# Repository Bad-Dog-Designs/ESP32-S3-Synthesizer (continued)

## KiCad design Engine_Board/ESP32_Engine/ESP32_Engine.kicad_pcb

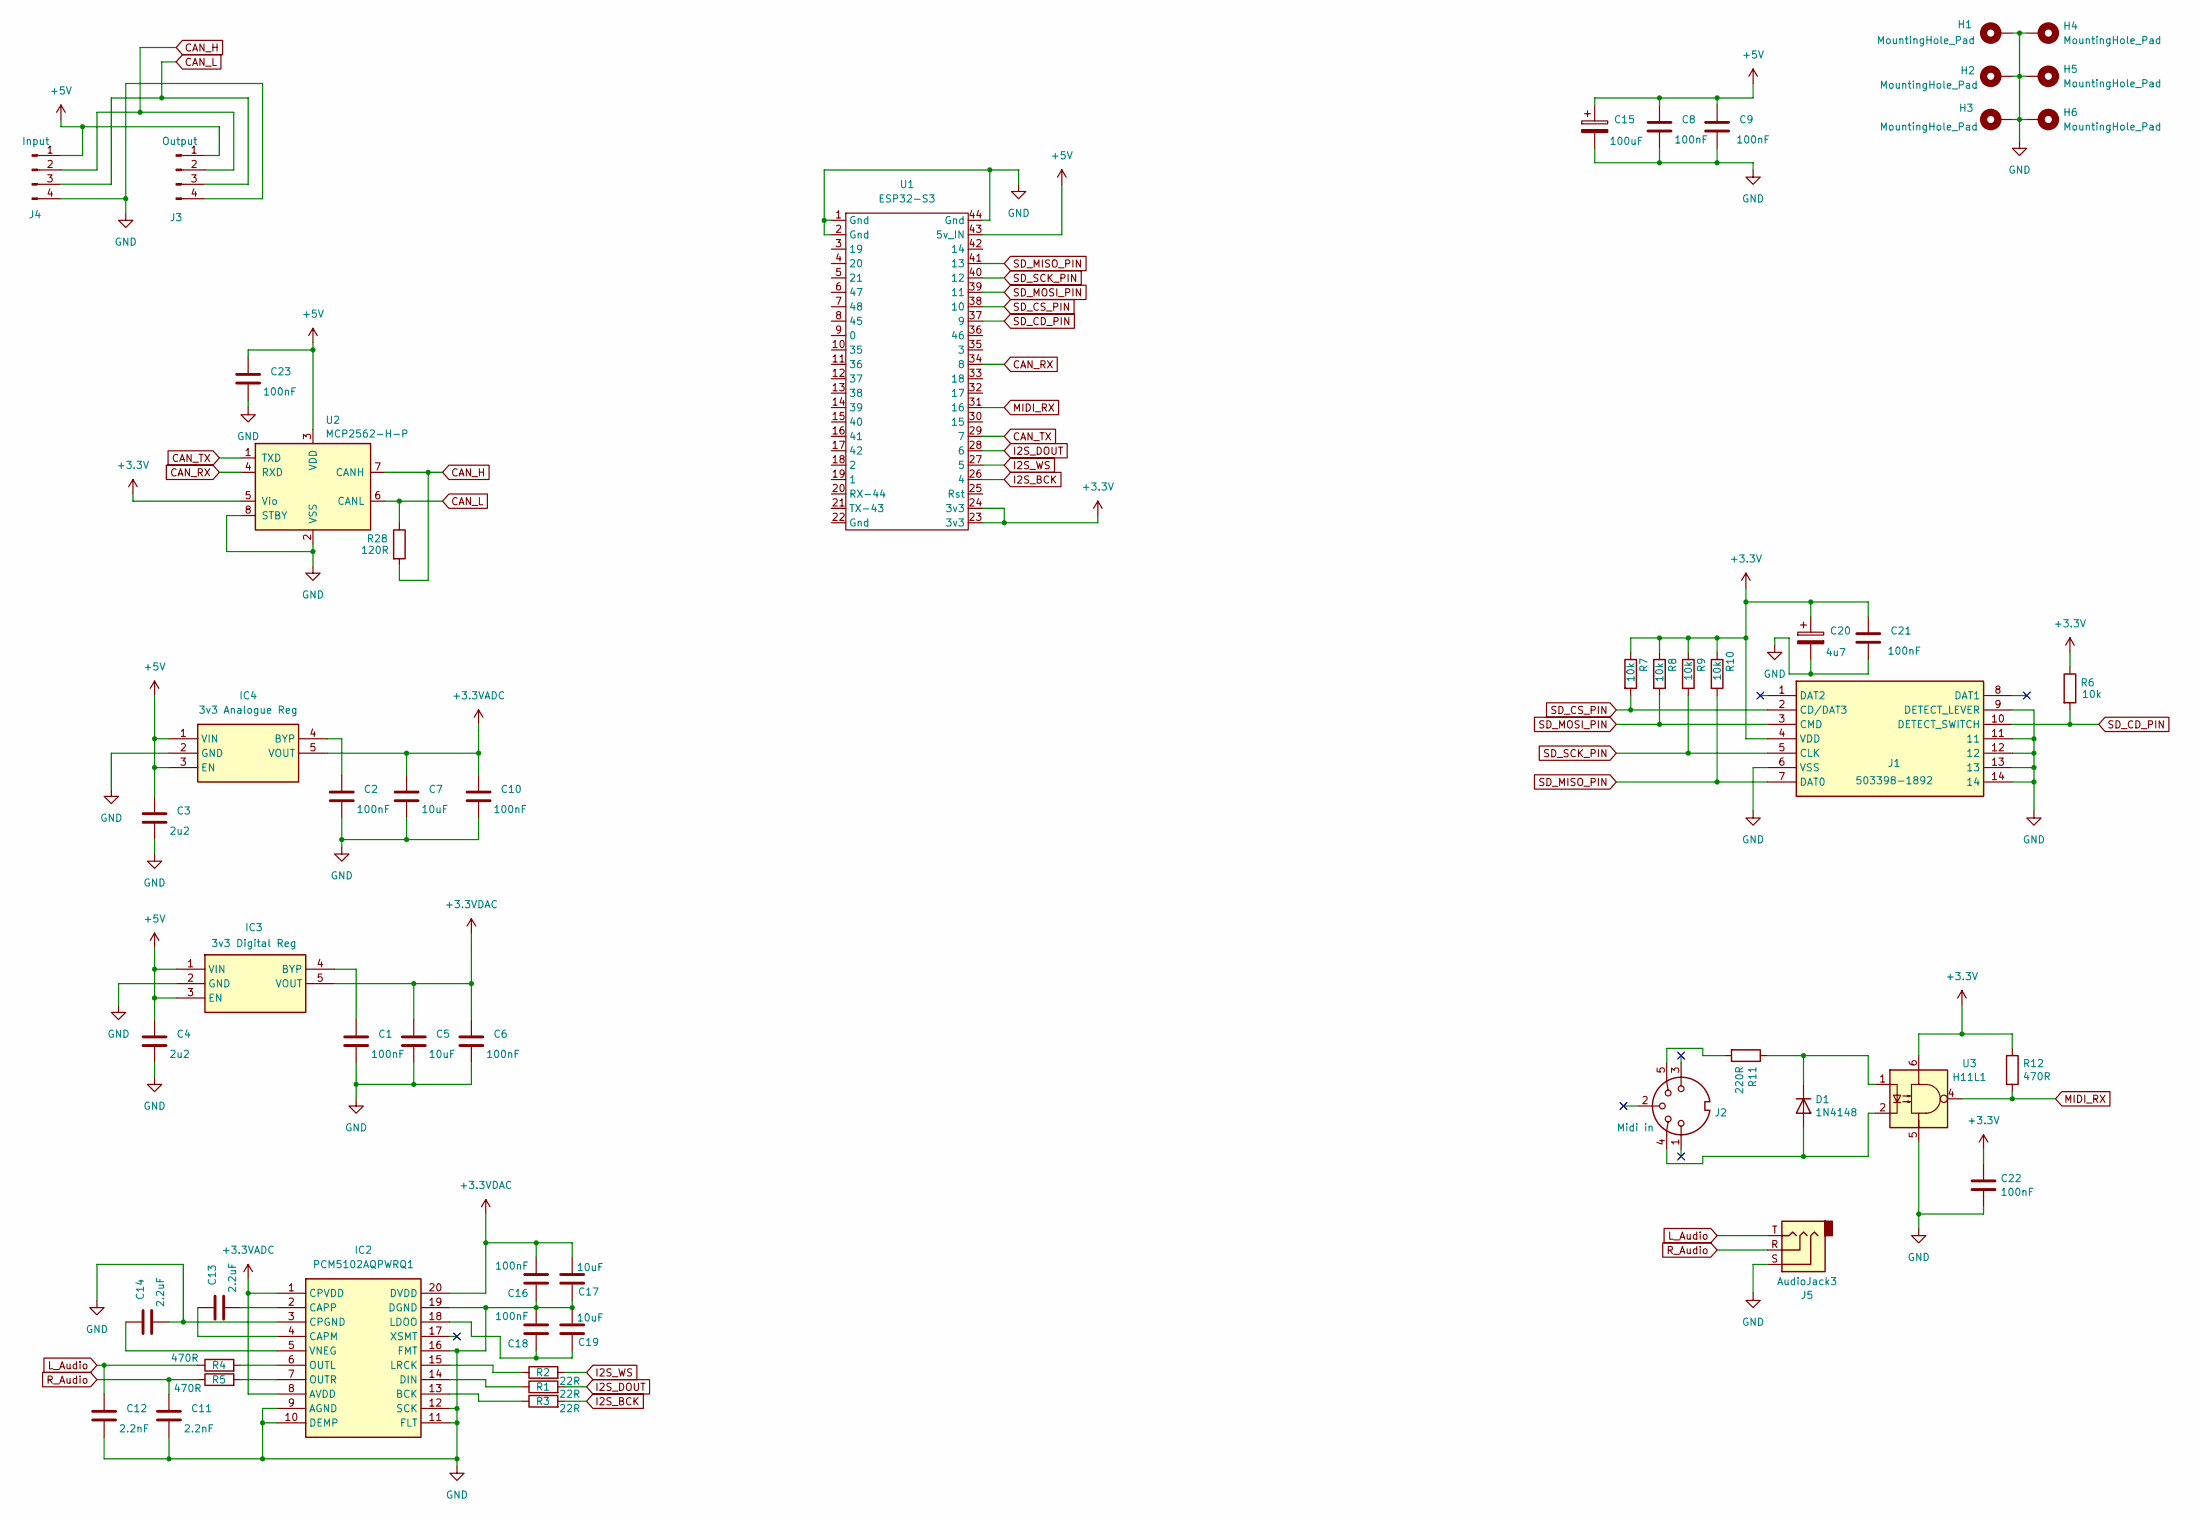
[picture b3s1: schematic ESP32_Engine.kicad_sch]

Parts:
C1, C2, C6, C10, C16, C18, C23: 100nF; C_0603_1608Metric_Pad1.08x0.95mm_HandSolder
C3, C4: 2u2; C_0805_2012Metric_Pad1.18x1.45mm_HandSolder
C5, C7, C17, C19: 10uF; C_0805_2012Metric_Pad1.18x1.45mm_HandSolder
C8, C9, C21: 100nF; C_0805_2012Metric_Pad1.18x1.45mm_HandSolder
C11, C12: 2.2nF; C_0603_1608Metric_Pad1.08x0.95mm_HandSolder
C13, C14: 2.2uF; C_0805_2012Metric_Pad1.18x1.45mm_HandSolder
C15: 100uF; CP_Radial_D4.0mm_P2.00mm
C20: 4u7; CP_Radial_D4.0mm_P2.00mm
C22: 100nF; C_0805_2012Metric
D1: 1N4148; D_MELF
H1, H2, H3, H4, H5, H6: MountingHole_Pad; MountingHole_3.2mm_M3_DIN965_Pad
IC2: PCM5102AQPWRQ1; SOP65P640X120-20N; Mouser Part Number 595-PCM5102AQPWRQ1
IC3: 3v3 Digital Reg; SOT95P280X100-5N; Mouser Part Number 998-MIC5323-3.3YD5TR
IC4: 3v3 Analogue Reg; SOT95P280X100-5N; Mouser Part Number 998-MIC5323-3.3YD5TR
J1: 503398-1892; 5033981892; Mouser Part Number 538-503398-1892
J2: Midi in; Midi_Socket
J3: Output; JST_EH_S4B-EH_1x04_P2.50mm_Horizontal
J4: Input; JST_EH_S4B-EH_1x04_P2.50mm_Horizontal
J5: AudioJack3; Jack_3.5mm_CUI_SJ1-3533NG_Horizontal
R1, R2, R3: 22R; R_0603_1608Metric_Pad0.98x0.95mm_HandSolder
R4, R5, R12: 470R; R_0603_1608Metric_Pad0.98x0.95mm_HandSolder
R6, R7, R8, R9, R10: 10k; R_0603_1608Metric_Pad0.98x0.95mm_HandSolder
R11: 220R; R_0603_1608Metric_Pad0.98x0.95mm_HandSolder
R28: 120R; R_0603_1608Metric_Pad0.98x0.95mm_HandSolder
U1: ESP32-S3; ESP32_S3
U2: MCP2562-H-P; DIP-8_W7.62mm
U3: H11L1; DIP-6_W7.62mm_SMDSocket_SmallPads

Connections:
+3.3V: C20.1, C21.1, C22.1, J1.4 (VDD), R6.1, R7.1, R8.1, R9.1, R10.1, R12.1, U1.23 (3v3), U1.24 (3v3), U2.5 (Vio), U3.6
+3.3VADC: C7.1, C10.1, IC2.1 (CPVDD), IC2.8 (AVDD), IC4.5 (VOUT)
+3.3VDAC: C5.1, C6.1, C16.2, C17.2, IC2.20 (DVDD), IC3.5 (VOUT)
+5V: C3.1, C4.1, C8.1, C9.1, C15.1, C23.1, IC3.1 (VIN), IC3.3 (EN), IC4.1 (VIN), IC4.3 (EN), J3.1, J4.1, U1.43 (5v_IN), U2.3 (VDD)
CAN_H: J3.2, J4.2, R28.2, U2.7 (CANH)
CAN_L: J3.3, J4.3, R28.1, U2.6 (CANL)
CAN_RX: U1.34 (8), U2.4 (RXD)
CAN_TX: U1.29 (7), U2.1 (TXD)
GND: C1.2, C2.2, C3.2, C4.2, C5.2, C6.2, C7.2, C8.2, C9.2, C10.2, C11.2, C12.2, C14.2, C15.2, C16.1, C17.1, C18.2, C19.2, C20.2, C21.2, C22.2, C23.2, H1.1, H2.1, H3.1, H4.1, H5.1, H6.1, IC2.3 (CPGND), IC2.9 (AGND), IC2.10 (DEMP), IC2.11 (FLT), IC2.12 (SCK), IC2.16 (FMT), IC2.19 (DGND), IC3.2 (GND), IC4.2 (GND), J1.6 (VSS), J1.9 (DETECT_LEVER), J1.11, J1.12, J1.13, J1.14, J2.6, J2.7, J3.4, J4.4, J5.S, U1.1 (Gnd), U1.2 (Gnd), U1.44 (Gnd), U2.2 (VSS), U2.8 (STBY), U3.5
I2S_BCK: R3.2, U1.26 (4)
I2S_DOUT: R1.2, U1.28 (6)
I2S_WS: R2.2, U1.27 (5)
L_Audio: C12.1, J5.T, R4.1
MIDI_RX: R12.2, U1.31 (16), U3.4
unnamed: D1.2 (A), J2.4, U3.2
unnamed: D1.1 (K), R11.1, U3.1
unnamed: IC2.13 (BCK), R3.1
unnamed: C13.1, IC2.4 (CAPM)
unnamed: C13.2, IC2.2 (CAPP)
unnamed: IC2.14 (DIN), R1.1
unnamed: C18.1, C19.1, IC2.18 (LDOO)
unnamed: IC2.15 (LRCK), R2.1
unnamed: IC2.6 (OUTL), R4.2
unnamed: IC2.7 (OUTR), R5.2
unnamed: C14.1, IC2.5 (VNEG)
unnamed: C1.1, IC3.4 (BYP)
unnamed: C2.1, IC4.4 (BYP)
unnamed: J2.5, R11.2
R_Audio: C11.1, J5.R, R5.1
SD_CD_PIN: J1.10 (DETECT_SWITCH), R6.2, U1.37 (9)
SD_CS_PIN: J1.2 (CD/DAT3), R7.2, U1.38 (10)
SD_MISO_PIN: J1.7 (DAT0), R10.2, U1.41 (13)
SD_MOSI_PIN: J1.3 (CMD), R8.2, U1.39 (11)
SD_SCK_PIN: J1.5 (CLK), R9.2, U1.40 (12)

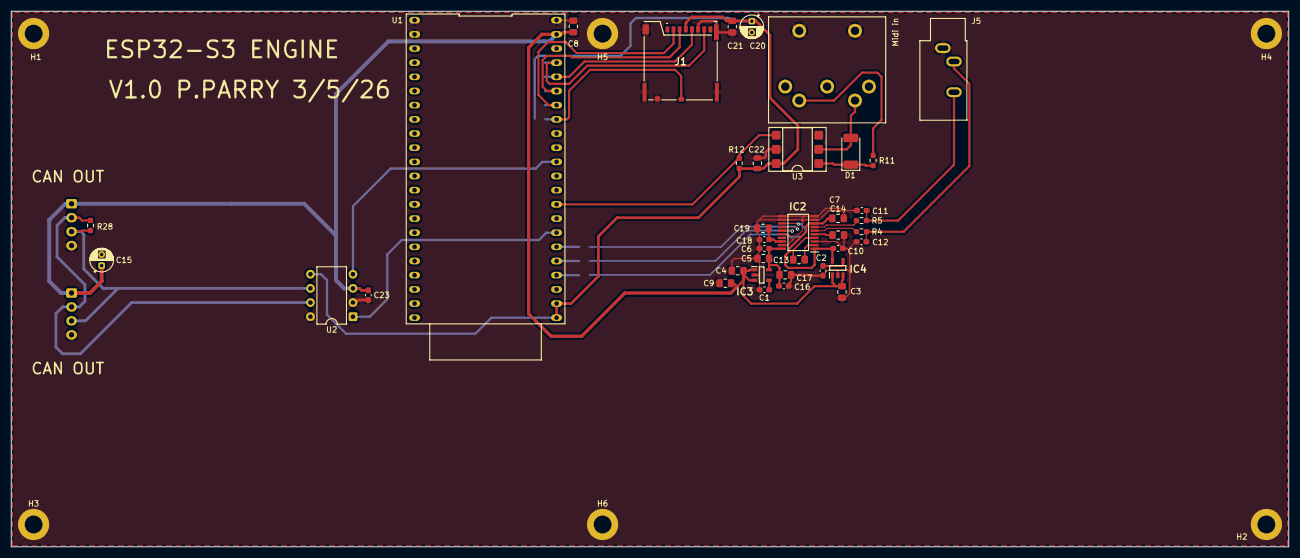
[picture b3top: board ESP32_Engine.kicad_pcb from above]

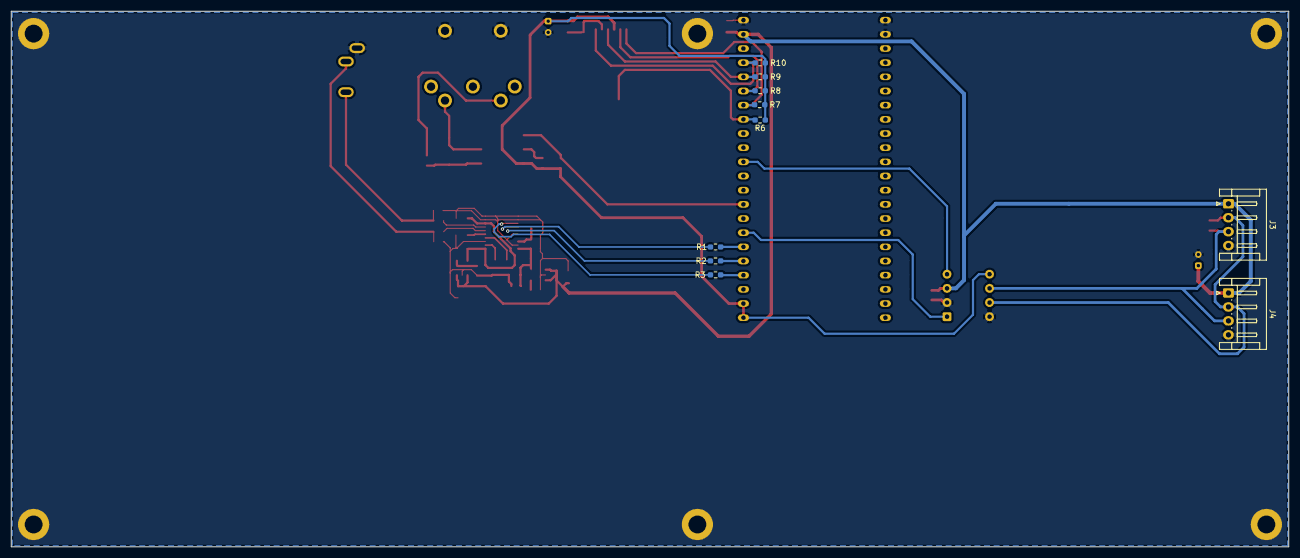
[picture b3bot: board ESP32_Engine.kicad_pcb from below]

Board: 2 copper layers, 229.0 x 96.0 mm, 54 parts (10 on the bottom side), 34 nets.

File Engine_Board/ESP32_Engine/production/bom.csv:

Designator,Footprint,Quantity,Value,LCSC Part #
"C1, C10, C16, C18, C2, C23, C6",0603,7,100nF,
"C11, C12",0603,2,2.2nF,
"C13, C14",0805,2,2.2uF,
C15,CP_Radial_D4.0mm_P2.00mm,1,100uF,
"C17, C19, C5, C7",0805,4,10uF,
C20,CP_Radial_D4.0mm_P2.00mm,1,4u7,
"C21, C22, C8, C9",0805,4,100nF,
"C3, C4",0805,2,2u2,
D1,D_MELF,1,1N4148,
IC2,SOP65P640X120-20N,1,PCM5102AQPWRQ1,
IC3,SOT95P280X100-5N,1,3v3 Digital Reg,
IC4,SOT95P280X100-5N,1,3v3 Analogue Reg,
J1,5033981892,1,503398-1892,
J2,Midi_Socket,1,Midi in,
J3,JST_EH_S4B-EH_1x04_P2.50mm_Horizontal,1,Output,
J4,JST_EH_S4B-EH_1x04_P2.50mm_Horizontal,1,Input,
J5,Jack_3.5mm_CUI_SJ1-3533NG_Horizontal,1,AudioJack3,
"R1, R2, R3",0603,3,22R,
"R10, R6, R7, R8, R9",0603,5,10k,
R11,0603,1,220R,
"R12, R4, R5",0603,3,470R,
R28,0603,1,120R,
U1,ESP32_S3,1,ESP32-S3,
U2,DIP-8_W7.62mm,1,MCP2562-H-P,
U3,DIP-6_W7.62mm_SMDSocket_SmallPads,1,H11L1,

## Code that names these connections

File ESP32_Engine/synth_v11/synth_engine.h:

#pragma once
// ==============================================================
// synth_engine.h  —  Version 11.0
// Voice, LFO, filter, oscillator and modulation routing types.
// Included by: synth_engine.cpp, synth_midi.cpp, synth_can.cpp, synth_v11.ino
// ==============================================================

#include <Arduino.h>
#include <math.h>
#include "synth_params.h"

// ==========================
// Configuration
// ==========================
#define SAMPLE_RATE  48000
#define TABLE_SIZE   1024
#define TABLE_BITS   10
#define MAX_VOICES   8    // Compile-time array size — actual active count is NUM_VOICES_ACTIVE
#define MAX_ROUTES   12   // Maximum simultaneous modulation routes

// ==========================
// SD Card Pins
// ==========================
#define SD_CD_PIN    9    // Card detect — LOW = card inserted (active low, internal pullup)
#define SD_CS_PIN    10
#define SD_MOSI_PIN  11
#define SD_SCK_PIN   12
#define SD_MISO_PIN  13

// ==========================
// Enumerations
// ==========================
enum OscType     { OSC_SAW, OSC_SINE, OSC_TRI, OSC_PULSE, OSC_CHAOS, OSC_NOISE };
enum FilterMode  { FILT_LOW, FILT_BAND, FILT_HIGH };
enum PlayMode    { MODE_POLY, MODE_DUO, MODE_UNISON };
enum EnvState    { ENV_IDLE, ENV_ATTACK, ENV_DECAY, ENV_SUSTAIN, ENV_RELEASE };

// 4 waveforms matching the hardware rotary switch: SINE=0 TRI=1 CHAOS=2 S&H=3
enum LFOWaveform { LFO_SINE, LFO_TRI, LFO_CHAOS, LFO_SH };

// ==========================
// LFO
// Note: no 'depth' field — modulation depth is per-route via Route.amount.
// RETRIGGER is a toggle: each PARAM_LFO_RETRIGGER message flips the state.
// ==========================
struct LFO
{
  float        rate      = 1.0f;   // Hz
  float        delay     = 0.0f;   // seconds before LFO fades in after note-on
  LFOWaveform  waveform  = LFO_SINE;
  bool         retrigger = false;  // true = reset phase on every note-on

  // Internal state — not user accessible
  float        phase      = 0.0f;  // running phase accumulator 0.0-1.0
  float        shValue    = 0.0f;  // held value for S+H waveform
  float        chaosX     = 0.5f;  // logistic map state for CHAOS waveform
  float        chaosR     = 3.7f;  // fixed default — not a real-time control
  float        delayTimer = 0.0f;  // counts up from 0 at note-on
};

// ==========================
// Modulation Route
// ==========================
// A route connects one source to one or more destinations simultaneously.
// oscMask selects which voices are affected (bit0=voice0/OSC1 .. bit5=voice5/OSC6).
// oscParamMask selects which parameters on those voices are modulated:
//   bit0=PITCH  bit1=PULSE_W  bit2=FOLD_AMOUNT
//   bit3=FOLD_BIAS or FM_RATIO (ESP32 checks voice.fmEnabled at modulation time)
//   bit4=CHAOS_R
//   bit5=SH_RATE or FM_DEPTH  (ESP32 checks voice.fmEnabled at modulation time)
//   bit6=LEVEL
// globalMask selects global destinations:
//   bit0=CUTOFF  bit1=RESONANCE  bit2=MASTER_LEVEL
//   bit3=UNI_DETUNE  bit4=LFO2_RATE
// amount: -1.0 to +1.0 (displayed as -99 to +99 on routing board)
// ==========================
struct Route
{
  bool    enabled      = false;
  uint8_t source       = ROUTE_SRC_LFO1;
  uint8_t oscMask      = 0;       // which voices are modulated
  uint8_t oscParamMask = 0;       // which OSC parameters are modulated
  uint8_t globalMask   = 0;       // which global parameters are modulated
  float   amount       = 0.0f;    // -1.0 to +1.0
};

// ==========================
// Ring Modulator
// ==========================
struct RingMod
{
  bool    enabled = false;
  uint8_t pair    = 0;      // 0=V0&V1  1=V2&V3  2=V0&V2  3=V1&V3
  float   level   = 1.0f;
  bool    modMute = false;  // true = modulator voice silent in final mix
};

// ==========================
// Voice
// ==========================
// PHASE NAMING:
//   phase       : uint32 running accumulator — INTERNAL, never user-accessible
//   phaseOffset : float 0.0-1.0, internal waveform start position at note-on
//
// CHAOS INTERNALS:
//   chaosR : user parameter (2.5-4.0)
//   chaosX : internal logistic map state, seeded from MIDI note — never user-accessible
//
// FM:
//   OSC_A (even voice) is the modulator: fmEnabled, fmDepth live here.
//   OSC_B (odd voice) is the carrier:    fmRatio lives here.
// ==========================
struct Voice
{
  // --- Core state (volatile: read Core 1, written Core 0) ---
  volatile uint32_t phase         = 0;
  volatile uint32_t phaseInc      = 0;
  volatile bool     active        = false;
  volatile uint8_t  note          = 255;
  volatile EnvState envState      = ENV_IDLE;
  volatile float    envLevel      = 0.0f;

  // --- Waveform ---
  OscType           oscType       = OSC_SAW;
  float             pulseWidth    = 0.5f;

  // --- Pitch ---
  int8_t            octave        = 0;      // -1, 0, +1
  float             detuneCents   = 0.0f;   // -50 to +50 cents
  float             phaseOffset   = 0.0f;   // internal waveform start 0.0-1.0

  // --- FM ---
  bool              fmEnabled     = false;  // OSC_A only: FM active for this board pair
  float             fmDepth       = 0.0f;   // OSC_A only: 0.0-1.0
  float             fmRatio       = 1.0f;   // OSC_B only: carrier:modulator ratio 0.5-8.0

  // --- Velocity ---
  // Normalised 0.0-1.0 at note-on. Scales voice output.
  // Also available as ROUTE_SRC_VELOCITY.
  float             velocity      = 1.0f;

  // --- Level ---
  float             level         = 1.0f;

  // --- Fold modifier ---
  // Post-oscillator, pre-filter. foldBias shifts fold point asymmetrically.
  bool              foldEnabled   = false;
  float             foldAmount    = 0.5f;   // 0.0 = passthrough, 1.0 = max folds
  float             foldBias      = 0.0f;   // -1.0 to +1.0

  // --- S+H modifier ---
  // Independent clock at shRate Hz updates phaseInc with a random pitch
  // within shRange semitones of rootFreq.
  bool              shEnabled     = false;
  uint32_t          shPhase       = 0;      // internal S+H clock accumulator
  float             shRate        = 4.0f;   // Hz
  float             shRange       = 24.0f;  // semitones

  // --- Hard sync ---
  // Even voices are always sync masters per board pair.
  // syncEnabled must only be set on odd voices.
  bool              syncEnabled   = false;

  // --- Solo ---
  bool              soloEnabled   = false;

  // --- Chaos waveform internals ---
  float             prevPhaseNorm = 0.0f;  // internal — for wrap detection
  float             chaosX        = 0.5f;  // internal — evolves autonomously
  float             chaosR        = 3.7f;  // user parameter

  // --- SVF Filter integrators (internal) ---
  float             fltLow        = 0.0f;
  float             fltBand       = 0.0f;
  float             fltF          = 0.1f;
  float             fltDamp       = 1.4f;

  // --- Root frequency ---
  float             rootFreq      = 440.0f;
};

// ==========================
// Global State — extern declarations
// All defined in synth_engine.cpp
// ==========================
extern uint8_t           NUM_VOICES_ACTIVE;
extern Voice             voices[MAX_VOICES];
extern portMUX_TYPE      voiceMux;
extern volatile PlayMode playMode;
extern FilterMode        filterMode;
extern float             cutoffHz;
extern float             resonance;
extern float             envAmount;
extern float             keyTracking;
extern float             unisonDetuneCents;
extern float             masterLevel;
extern float             attackTime;
extern float             decayTime;
extern float             sustainLevel;
extern float             releaseTime;
extern float             attackCoeff;
extern float             decayCoeff;
extern float             releaseCoeff;
extern LFO               lfo1;
extern LFO               lfo2;
extern RingMod           ringMod;
extern Route             routes[MAX_ROUTES];
extern float             modWheelValue;        // MIDI CC1, normalised 0.0-1.0
extern float             tableA[TABLE_SIZE];
extern TaskHandle_t      audioTaskHandle;
extern bool              routingBoardDetected; // true if routing board responded at startup
extern bool              cloneActive;          // true = clone is active, all clone LEDs lit

// ==========================
// Function Declarations
// ==========================
void     setupI2S();
void     initWavetable();
void     updateEnvelopeRates();
void     updateFilterCoeffs(Voice &v);
float    midiToFreq(uint8_t note);
uint32_t freqToPhaseInc(float freq);
float    centsToRatio(float cents);
uint32_t shRandomPhaseInc(float rootFreq, float shRange);
float    chaosSeedFromNote(uint8_t note);
uint32_t voicePhaseInc(float baseFreq, int8_t octave, float detuneCents);
void     allNotesOff();
void     cloneVoice(uint8_t src);
int      allocateVoice();
int      allocateVoiceInGroup(int groupStart, int groupEnd);
void     audioTask(void *parameter);

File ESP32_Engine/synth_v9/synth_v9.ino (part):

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// --- I2S Pins (ESP32-S3) ---
// GPIO 25/26 do not exist on S3 — reassigned to safe GPIOs.
// Avoid: 0, 3, 19, 20, 45, 46 (boot/USB), 35-37 (PSRAM if fitted)
#define I2S_BCK         4
#define I2S_WS          5
#define I2S_DOUT        6

// --- MIDI ---
#define MIDI_BAUD       31250
#define MIDI_RX_PIN     16

// --- TWAI (CAN) Pins ---
#define TWAI_TX_PIN     GPIO_NUM_7
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void setup()
{
  Serial.begin(115200);
  Serial2.begin(MIDI_BAUD, SERIAL_8N1, MIDI_RX_PIN, -1);

  srand(esp_random());

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
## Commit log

2026-05-03 Create AT238p_OSCILLATOR
    Folder for the At328p source code for the Oscillator board
2026-05-04 Replaced repo with correct structure and files
2026-05-05 Updated Readme for Project overview
